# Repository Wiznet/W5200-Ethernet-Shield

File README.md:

# W5200 Ethernet Shield
W5200 Ethernet Shield is compatible with Official [Arduino Ethernet Shield](http://arduino.cc/en/Main/ArduinoEthernetShield) and support fast SPI and 8 sockets. 

## Hardware
These are PCB files for the W5200 Ethernet Shield for Arduino. The files were created in the free & low cost EagleCad software available from [CadSoft](http://www.cadsoftusa.com/download-eagle/?language=en).

## Software
You need to change the existing W5100 files to W5200 library files.

1. Install W5200 library
   Overwrite w5100.cpp, w5100.h to the "/libraries/Ethernet/utility" folder in your Arduino IDE. 

2. Using the W5200 library and evaluate existing Ethernet example.
   In the Arduino IDE, go to Files->Examples->Ethernet and open any example, compile and upload the file to Arduino board.

3. Note: libraries/Ethernet/Ethernet.h needs the following at line 10 instead of #define MAX_SOCK_NUM 4, since it doesn't #include "w5100.h" anymore:

 `#ifdef W5200`

 `#define MAX_SOCK_NUM 8`

 `#else`
 
 `#define MAX_SOCK_NUM 4`

 `#endif`

## Revision History
Initial Release : 10 June 2013

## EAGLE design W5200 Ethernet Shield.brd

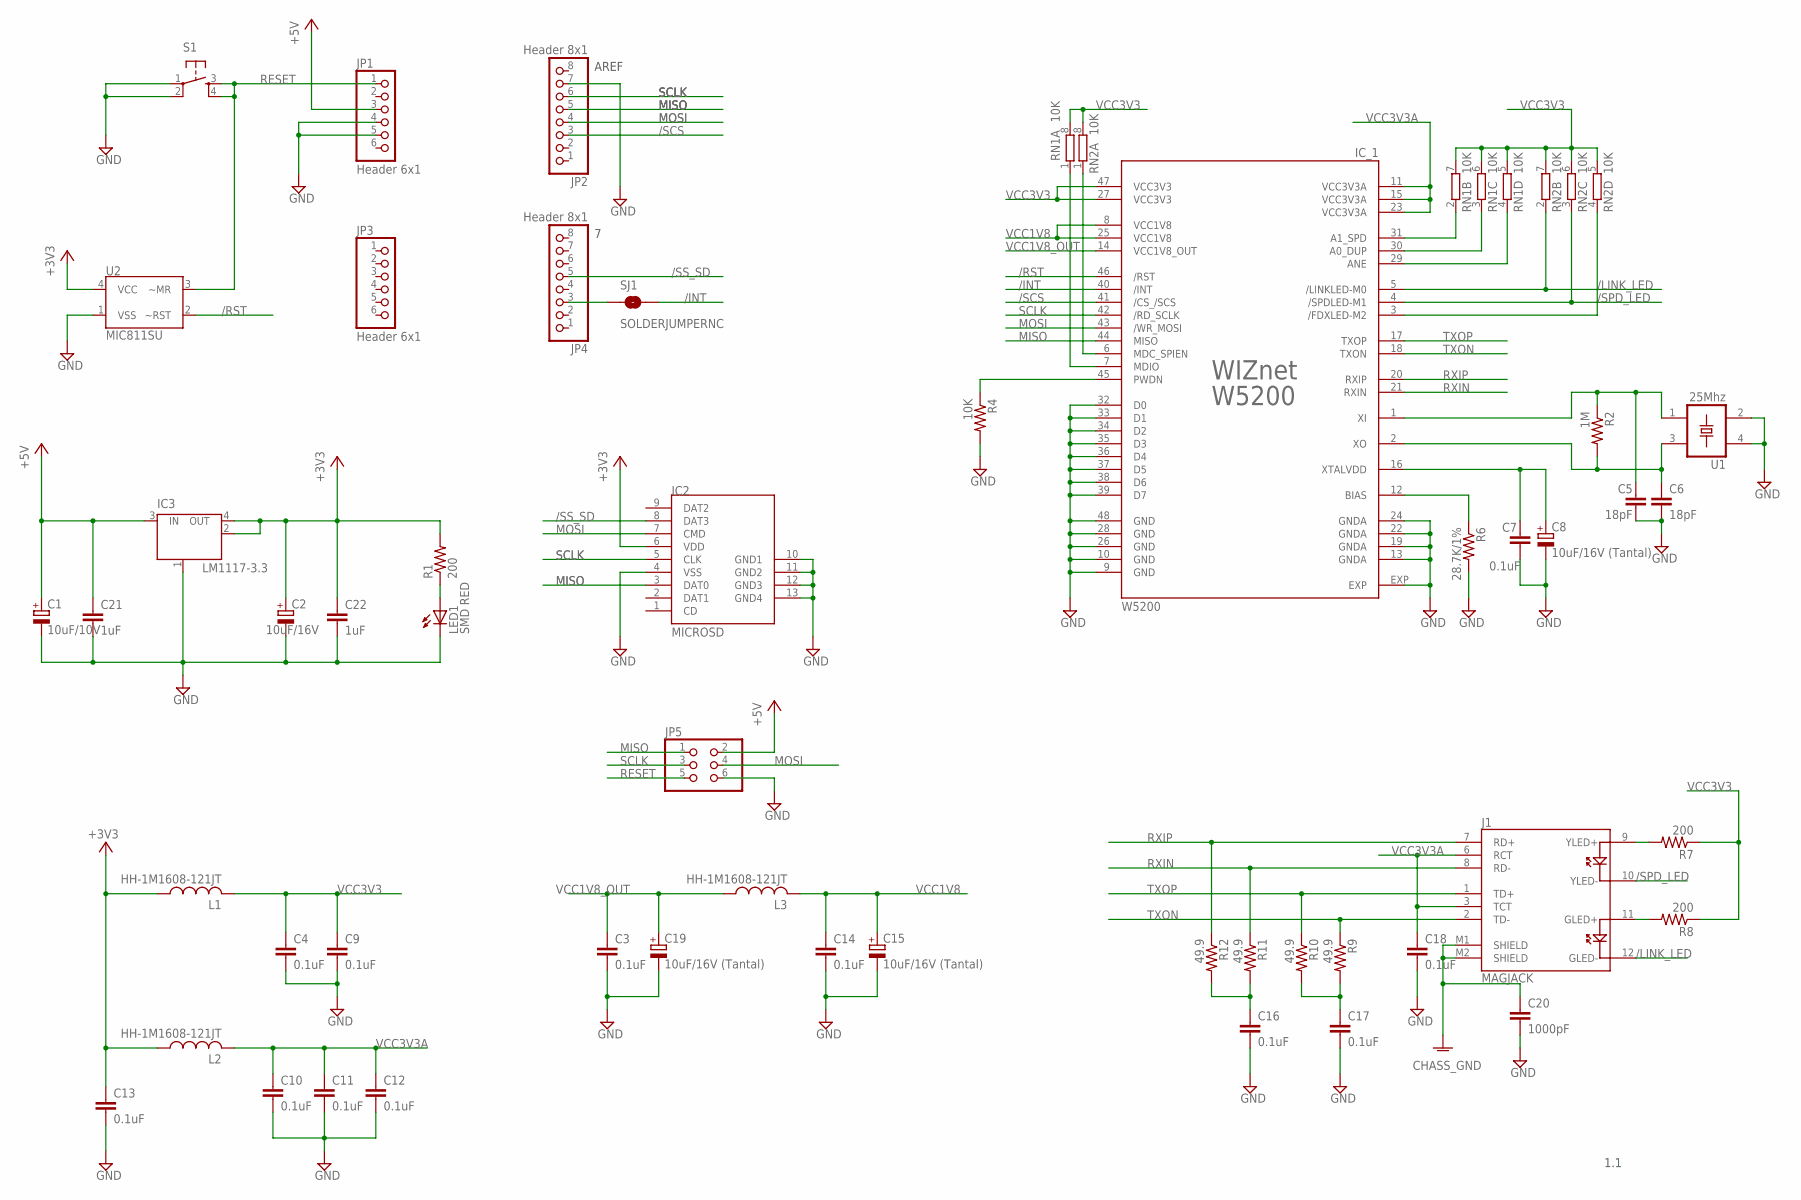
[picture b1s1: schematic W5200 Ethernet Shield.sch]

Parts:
C1: 10uF/10V; CT3216
C2: 10uF/16V; CT3216
C3, C4, C7, C9, C10, C11, C12, C13, C14, C16, C17, C18: 0.1uF; C0603
C5, C6: 18pF; C0603
C8, C15, C19: 10uF/16V (Tantal); CT3216
C20: 1000pF; C3225
C21, C22: 1uF; C0603
IC2: MICROSD; MSD_SYMBOL_MSDPAC
IC3: LM1117-3.3; SOT223
IC_1: W5200; QFN48
J1: MAGJACK
JP1, JP3: Header 6x1; 1X06
JP2, JP4: Header 8x1; 1X08
JP5: PINHD-2X3; 2X03
L1, L2, L3: HH-1M1608-121JT; L2012C
LED1: SMD RED; CHIP-LED0805
R1, R7, R8: 200; R0603
R2: 1M; R0603
R4: 10K; R0603
R6: 28.7K/1%; R0603
R9, R10, R11, R12: 49.9; R0603
RN1, RN2: 10K; EXBV8V
S1: TAC_SWITCHSMD; TACTILE_SWITCH_SMD
SJ1: SOLDERJUMPERNC; SJ_2S
U1: 25Mhz; CRYSTAL
U2: MIC811SU; SOT143

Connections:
+3V3: C2.+, C13.1, C22.1, IC2.6 (VDD), IC3.2 (OUT), IC3.4 (OUT), L1.1, L2.1, R1.2, U2.4 (VCC)
+5V: C1.+, C21.1, IC3.3 (IN), JP1.3, JP5.2
/INT: IC_1.40 (/INT), SJ1.2
/LINK_LED: IC_1.5 (/LINKLED-M0), J1.12 (GLED-), RN2.2 (1)
/RST: IC_1.46 (/RST), U2.2 (~RST)
/SCS: IC_1.41 (/CS_/SCS), JP2.3
/SPD_LED: IC_1.4 (/SPDLED-M1), J1.10 (YLED-), RN2.3 (1)
/SS_SD: IC2.8 (DAT3), JP4.5
GND: C1.-, C2.-, C3.2, C4.2, C5.2, C6.2, C7.2, C8.-, C9.2, C10.2, C11.2, C12.2, C13.2, C14.2, C15.-, C16.2, C17.2, C18.2, C19.-, C20.2, C21.2, C22.2, IC2.4 (VSS), IC2.10 (GND1), IC2.11 (GND2), IC2.12 (GND3), IC2.13 (GND4), IC3.1 (GND/ADJ), IC_1.9 (GND), IC_1.10 (GND), IC_1.13 (GNDA), IC_1.19 (GNDA), IC_1.22 (GNDA), IC_1.24 (GNDA), IC_1.26 (GND), IC_1.28 (GND), IC_1.32 (D0), IC_1.33 (D1), IC_1.34 (D2), IC_1.35 (D3), IC_1.36 (D4), IC_1.37 (D5), IC_1.38 (D6), IC_1.39 (D7), IC_1.48 (GND), IC_1.EXP, JP1.4, JP1.5, JP2.7, JP5.6, LED1.C, R4.2, R6.2, S1.1, S1.2, U1.2 (GND0), U1.4 (GND1), U2.1 (VSS)
GNDA: C20.1, J1.M1 (SHIELD), J1.M2 (SHIELD)
MISO: IC2.3 (DAT0), IC_1.44 (MISO), JP2.5, JP5.1
MOSI: IC2.7 (CMD), IC_1.43 (/WR_MOSI), JP2.4, JP5.4
unnamed: JP4.3, SJ1.1
unnamed: IC_1.31 (A1_SPD), RN1.2 (1)
unnamed: C6.1, IC_1.2 (XO), R2.2, U1.3 (OUT)
unnamed: C5.1, IC_1.1 (XI), R2.1, U1.1 (TRI)
unnamed: IC_1.30 (A0_DUP), RN1.3 (1)
unnamed: IC_1.29 (ANE), RN1.4 (1)
unnamed: J1.9 (YLED+), R7.2
unnamed: J1.11 (GLED+), R8.2
unnamed: IC_1.7 (MDIO), RN1.1
unnamed: IC_1.12 (BIAS), R6.1
unnamed: C7.1, C8.+, IC_1.16 (XTALVDD)
unnamed: C17.1, R9.2, R10.2
unnamed: LED1.A, R1.1
unnamed: C16.1, R11.2, R12.2
unnamed: IC_1.6 (MDC_SPIEN), RN2.1
unnamed: IC_1.3 (/FDXLED-M2), RN2.4 (1)
PWDN: IC_1.45 (PWDN), R4.1
RESET: JP1.1, JP5.5, S1.3, S1.4, U2.3 (~MR)
RXIN: IC_1.21 (RXIN), J1.8 (RD-), R11.1
RXIP: IC_1.20 (RXIP), J1.7 (RD+), R12.1
SCLK: IC2.5 (CLK), IC_1.42 (/RD_SCLK), JP2.6, JP5.3
TXON: IC_1.18 (TXON), J1.2 (TD-), R9.1
TXOP: IC_1.17 (TXOP), J1.1 (TD+), R10.1
VCC1V8: C14.1, C15.+, IC_1.8 (VCC1V8), IC_1.25 (VCC1V8), L3.2
VCC1V8_OUT: C3.1, C19.+, IC_1.14 (VCC1V8_OUT), L3.1
VCC3V3: C4.1, C9.1, IC_1.27 (VCC3V3), IC_1.47 (VCC3V3), L1.2, R7.1, R8.1, RN1.5 (2), RN1.6 (2), RN1.7 (2), RN1.8 (2), RN2.5 (2), RN2.6 (2), RN2.7 (2), RN2.8 (2)
VCC3V3A: C10.1, C11.1, C12.1, C18.1, IC_1.11 (VCC3V3A), IC_1.15 (VCC3V3A), IC_1.23 (VCC3V3A), J1.3 (TCT), J1.6 (RCT), L2.2

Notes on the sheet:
AREF
SCLK
MISO
MOSI
1.1

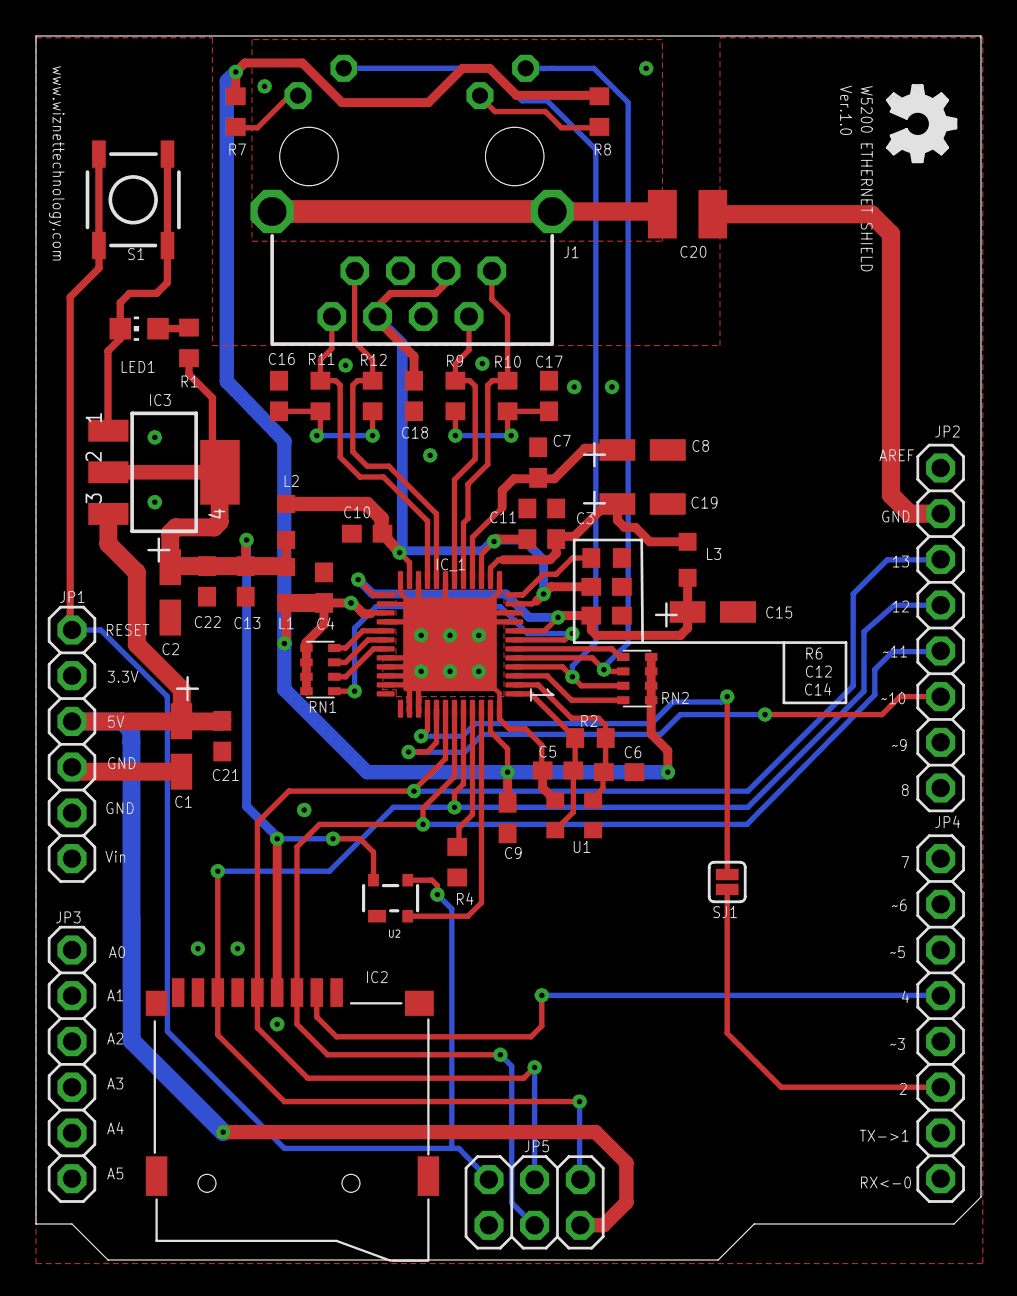
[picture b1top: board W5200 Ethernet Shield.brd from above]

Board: 2 copper layers, 52.5 x 68.0 mm, 52 parts (0 on the bottom side), 39 nets.

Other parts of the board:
U$1: OSHW_FILLX150_NOTEXT

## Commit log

2013-06-10 Initial release
2013-07-22 Adding S/W lib
2013-10-11 update code for Arduino Due

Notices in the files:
parts and their libraries:
SparkFun: Licensing: CC v3.0 Share-Alike You are welcome to use this library for commercial purposes.
